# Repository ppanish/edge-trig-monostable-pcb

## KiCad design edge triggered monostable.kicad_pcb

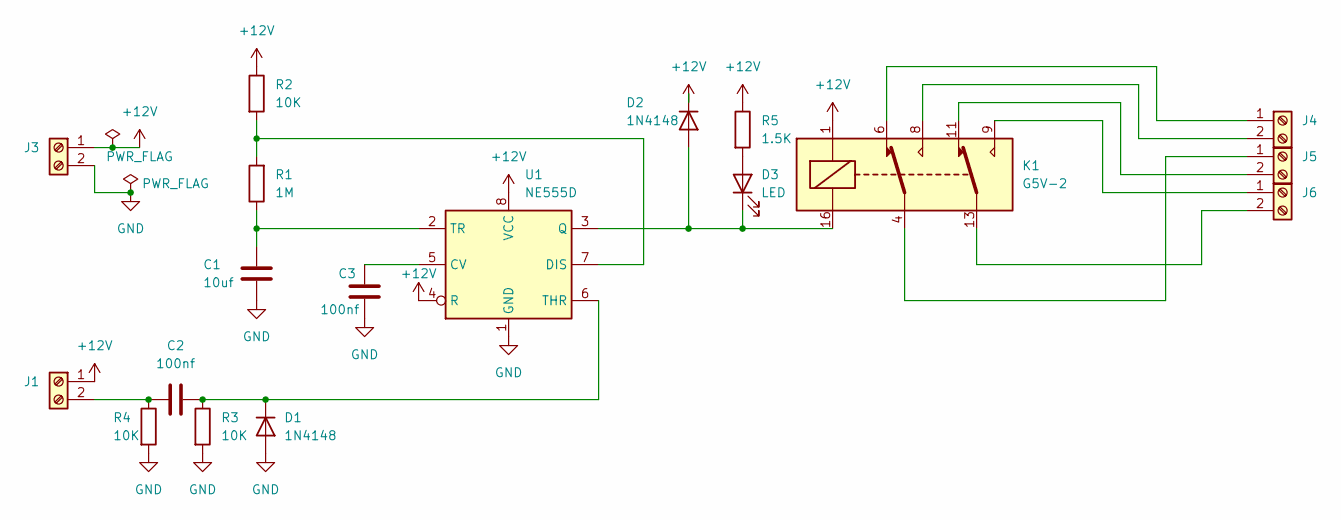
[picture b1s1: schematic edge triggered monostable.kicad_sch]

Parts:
C1: 10uf; C_0805_2012Metric; LCSC C440198
C2, C3: 100nf; C_0805_2012Metric; LCSC C49678
D1, D2: 1N4148; D_SOD-123; LCSC C81598
D3: LED; LED_0805_2012Metric; LCSC C84256
J1, J3, J4, J5, J6: Screw_Terminal_01x02; TerminalBlock_TE_282834-2_1x02_P2.54mm_Horizontal; LCSC C2922597
K1: G5V-2; Relay_DPDT_Omron_G5V-2; LCSC C28089
R1: 1M; R_0805_2012Metric; LCSC C17514
R2, R3, R4: 10K; R_0805_2012Metric; LCSC C17414
R5: 1.5K; R_0805_2012Metric; LCSC C4310
U1: NE555D; SOIC-8_3.9x4.9mm_P1.27mm; LCSC C7593

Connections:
+12V: D2.1 (K), J1.1, J3.1, K1.1, R2.1, R5.1, U1.4 (R), U1.8 (VCC)
GND: C1.2, C3.2, D1.2 (A), J3.2, R3.2, R4.2, U1.1 (GND)
unnamed: C2.2, D1.1 (K), R3.1, U1.6 (THR)
unnamed: D2.2 (A), D3.1 (K), K1.16, U1.3 (Q)
unnamed: D3.2 (A), R5.2
unnamed: C2.1, J1.2, R4.1
unnamed: J4.1, K1.6
unnamed: J4.2, K1.8
unnamed: J5.1, K1.4
unnamed: J5.2, K1.11
unnamed: J6.1, K1.9
unnamed: J6.2, K1.13
unnamed: C3.1, U1.5 (CV)
unnamed: R1.2, R2.2, U1.7 (DIS)
unnamed: C1.1, R1.1, U1.2 (TR)

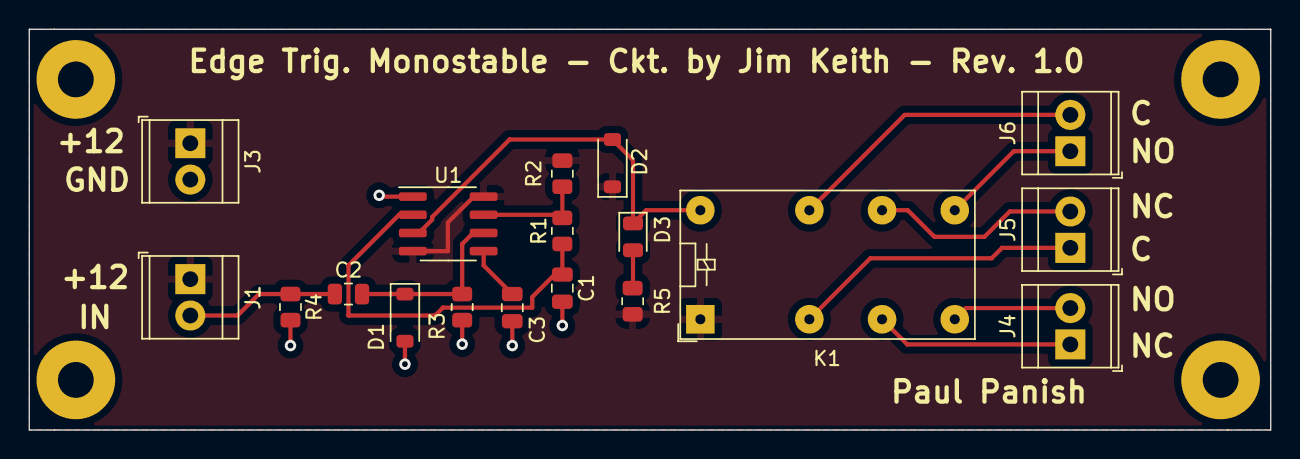
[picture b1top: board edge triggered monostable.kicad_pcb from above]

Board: 2 copper layers, 86.8 x 28.0 mm, 18 parts (0 on the bottom side), 15 nets.

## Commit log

2023-08-01 First pass pcb layout
2023-08-06 Completed board design and build files
2023-08-09 Added LED, BOM, and position files...
2023-08-27 First board release. Order has been placed.
